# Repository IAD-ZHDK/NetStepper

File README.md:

# Net Stepper

**A networked stepper motor controller.**

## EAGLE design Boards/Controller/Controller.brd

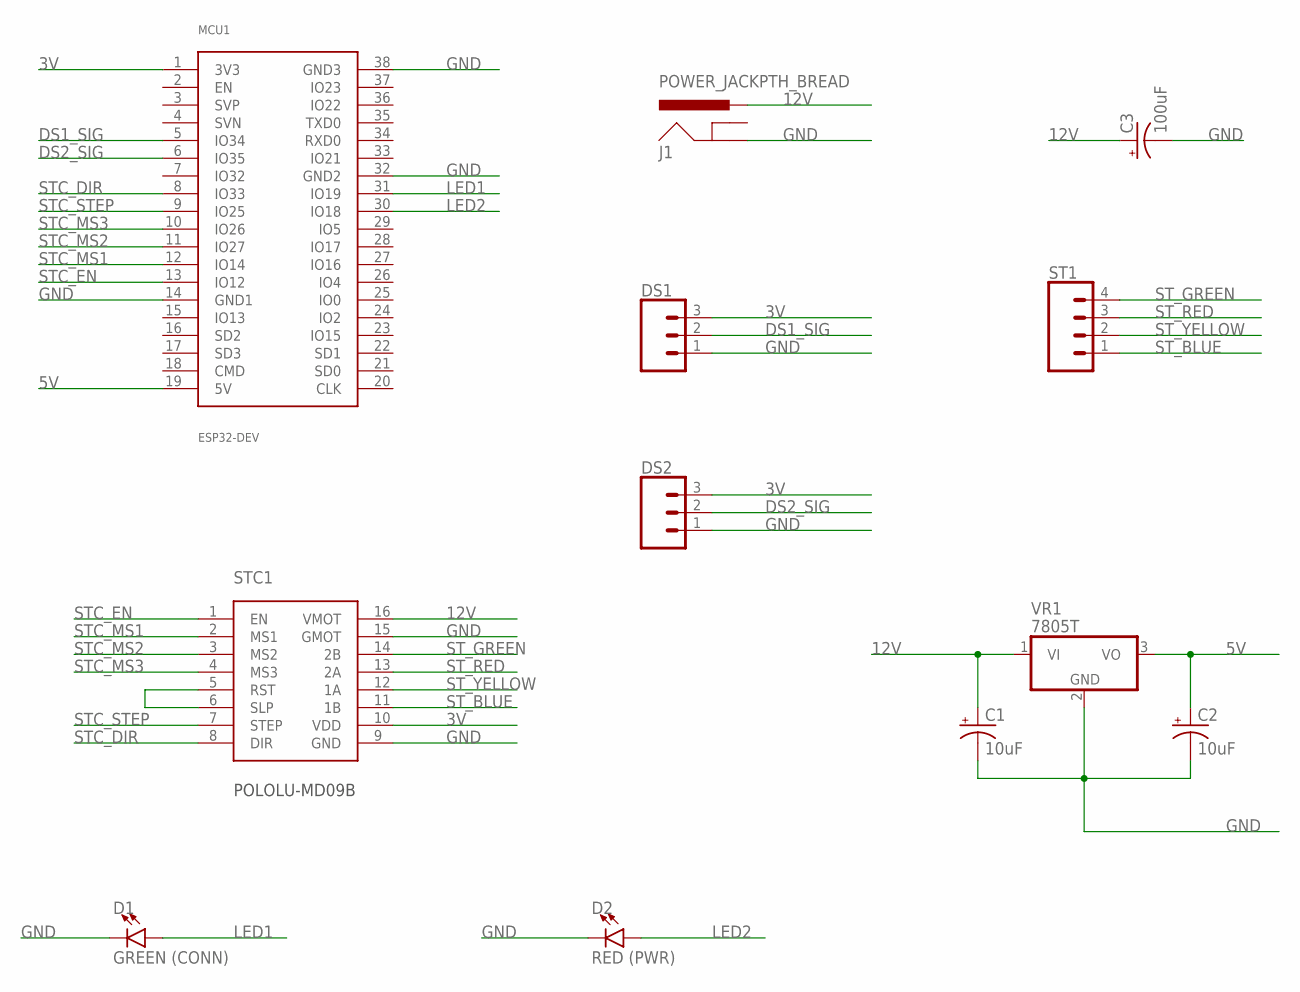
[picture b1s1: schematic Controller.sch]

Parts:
C1, C2: 10uF; E2-5
C3: 100uF; E2-5
D1: GREEN (CONN); LED_5MM
D2: RED (PWR); LED_5MM
DS1, DS2: CONN_03LONGPADS; 1X03_LONGPADS
J1: POWER_JACKPTH_BREAD; POWER_JACK_PTH_BREAD
MCU1: ESP32-DEV
ST1: CONN_04LONGPADS; 1X04_LONGPADS
STC1: POLOLU-MD09B
VR1: 7805T; TO220H

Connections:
3V: DS1.3, DS2.3, MCU1.1 (3V3), STC1.10 (VDD)
5V: C2.+, MCU1.19 (5V), VR1.3 (VO)
12V: C1.+, C3.+, J1.PWR, STC1.16 (VMOT), VR1.1 (VI)
DS1_SIG: DS1.2, MCU1.5 (IO34)
DS2_SIG: DS2.2, MCU1.6 (IO35)
GND: C1.-, C2.-, C3.-, D1.K (C), D2.K (C), DS1.1, DS2.1, J1.GND, MCU1.14 (GND1), MCU1.32 (GND2), MCU1.38 (GND3), STC1.9 (GND), STC1.15 (GMOT), VR1.2 (GND)
LED1: D1.A, MCU1.31 (IO19)
LED2: D2.A, MCU1.30 (IO18)
unnamed: STC1.5 (RST), STC1.6 (SLP)
STC_DIR: MCU1.8 (IO33), STC1.8 (DIR)
STC_EN: MCU1.13 (IO12), STC1.1 (EN)
STC_MS1: MCU1.12 (IO14), STC1.2 (MS1)
STC_MS2: MCU1.11 (IO27), STC1.3 (MS2)
STC_MS3: MCU1.10 (IO26), STC1.4 (MS3)
STC_STEP: MCU1.9 (IO25), STC1.7 (STEP)
ST_BLUE: ST1.1, STC1.11 (1B)
ST_GREEN: ST1.4, STC1.14 (2B)
ST_RED: ST1.3, STC1.13 (2A)
ST_YELLOW: ST1.2, STC1.12 (1A)

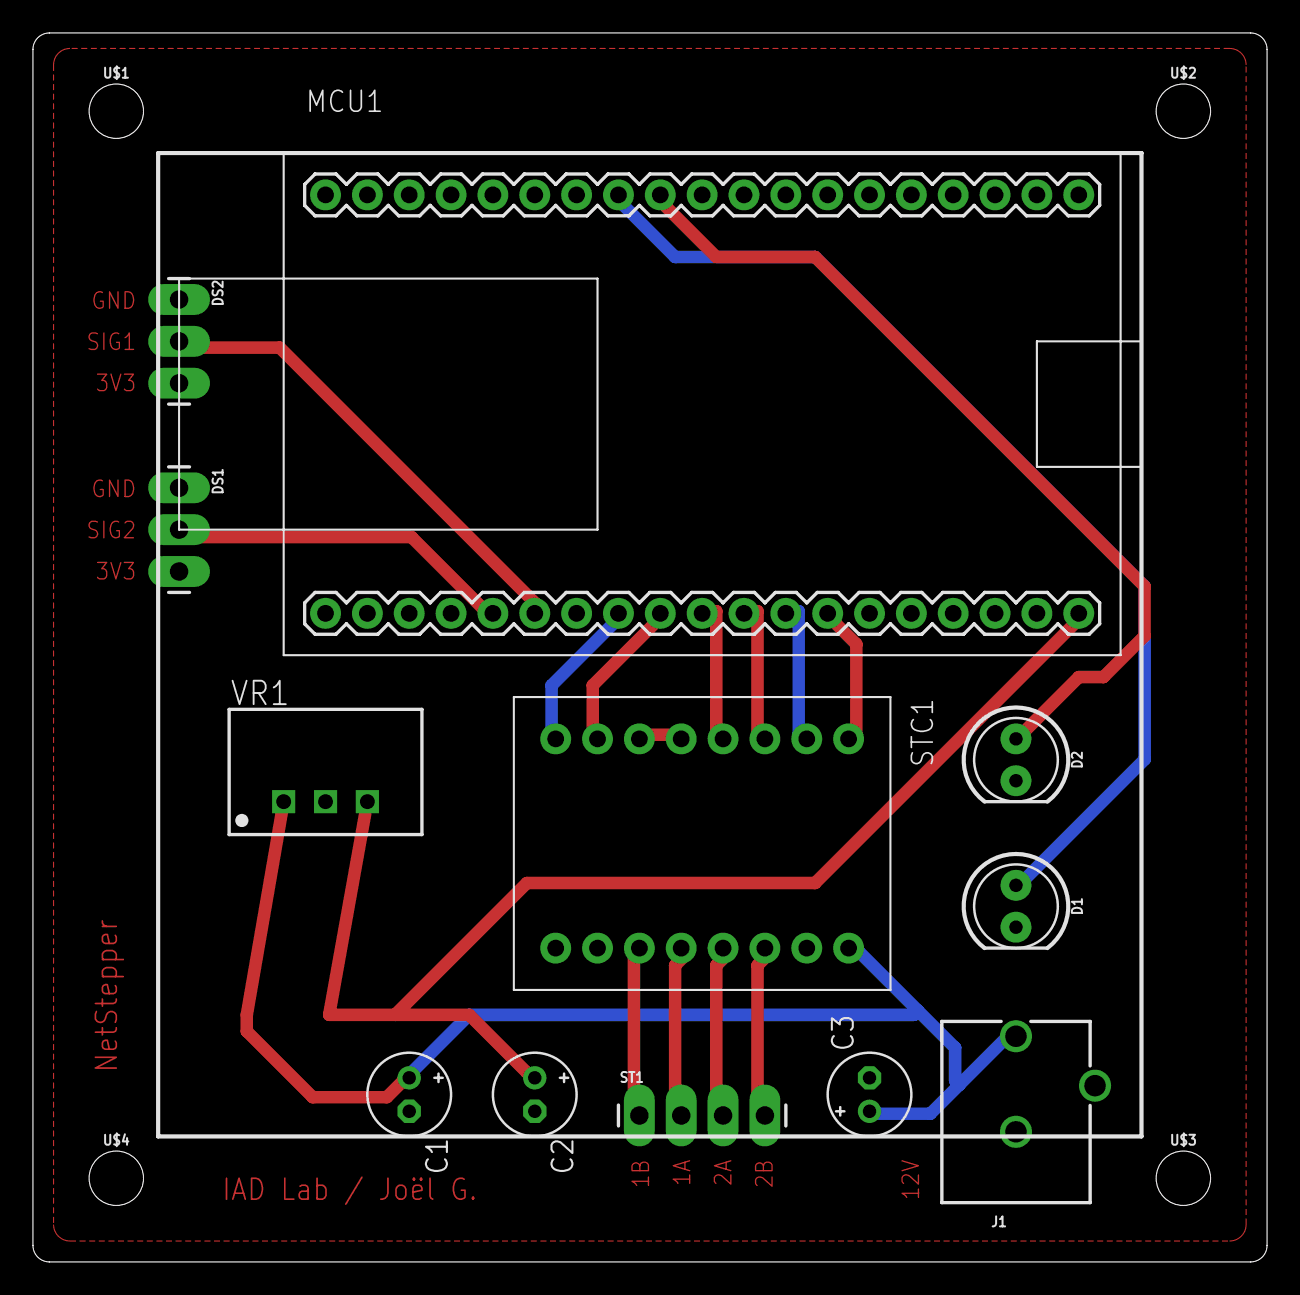
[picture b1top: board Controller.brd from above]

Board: 2 copper layers, 74.9 x 74.6 mm, 16 parts (0 on the bottom side), 19 nets.

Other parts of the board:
U$1, U$2, U$3, U$4: STAND-OFF

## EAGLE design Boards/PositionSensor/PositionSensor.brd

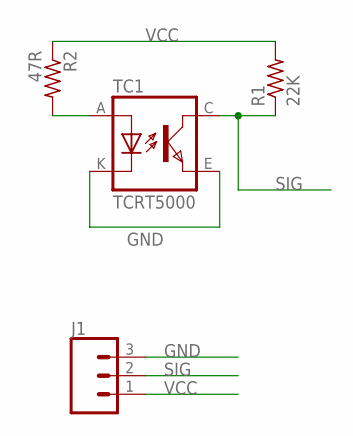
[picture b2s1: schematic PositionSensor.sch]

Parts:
J1: CONN_03LONGPADS; 1X03_LONGPADS
R1: 22K; 0204/7
R2: 47R; 0204/7
TC1: TCRT5000

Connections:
GND: J1.3, TC1.E (EMITTER), TC1.K (CATHODE)
unnamed: R2.2, TC1.A (ANODE)
SIG: J1.2, R1.1, TC1.C (COLLECTOR)
VCC: J1.1, R1.2, R2.1

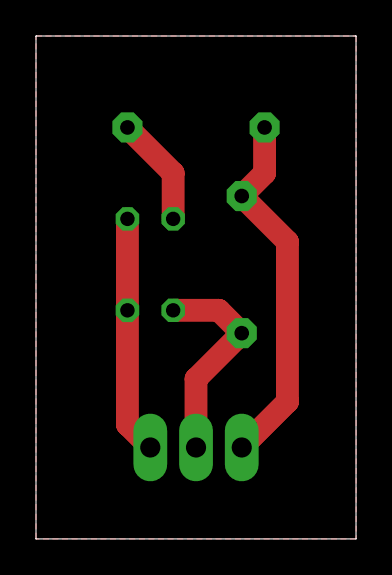
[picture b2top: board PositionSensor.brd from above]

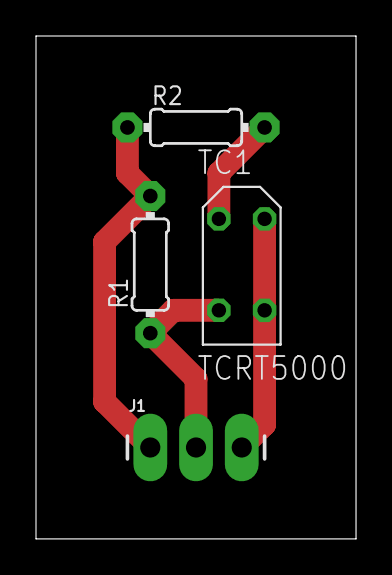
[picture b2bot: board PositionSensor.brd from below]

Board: 2 copper layers, 17.8 x 27.9 mm, 4 parts (4 on the bottom side), 4 nets.

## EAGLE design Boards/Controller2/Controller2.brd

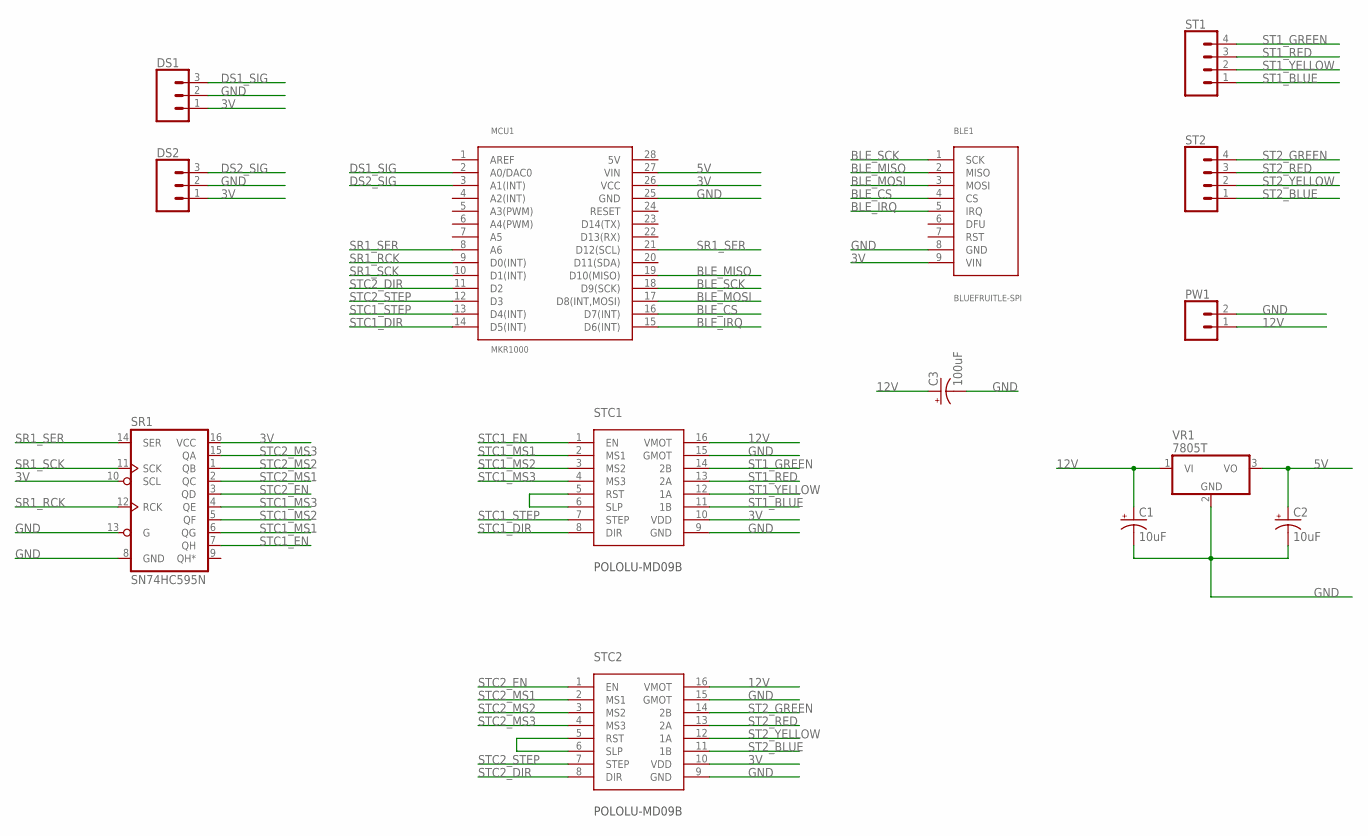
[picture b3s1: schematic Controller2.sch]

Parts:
BLE1: BLUEFRUITLE-SPI; BLUEFRUITLE-SPI-SOCKET
C1, C2: 10uF; E2-5
C3: 100uF; E2-5
DS1, DS2: CONN_03LONGPADS; 1X03_LONGPADS
MCU1: MKR1000; MKR1000-SOCKET
PW1: CONN_025MM; SCREWTERMINAL-5MM-2
SR1: SN74HC595N; DIP16
ST1, ST2: CONN_04LONGPADS; 1X04_LONGPADS
STC1, STC2: POLOLU-MD09B
VR1: 7805T; TO220H

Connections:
3V: BLE1.9 (VIN), DS1.1, DS2.1, MCU1.26 (VCC), SR1.10 (SCL), SR1.16 (VCC), STC1.10 (VDD), STC2.10 (VDD)
5V: C2.+, MCU1.27 (VIN), VR1.3 (VO)
12V: C1.+, C3.+, PW1.1, STC1.16 (VMOT), STC2.16 (VMOT), VR1.1 (VI)
BLE_CS: BLE1.4 (CS), MCU1.16 (D7(INT))
BLE_IRQ: BLE1.5 (IRQ), MCU1.15 (D6(INT))
BLE_MISO: BLE1.2 (MISO), MCU1.19 (D10(MISO))
BLE_MOSI: BLE1.3 (MOSI), MCU1.17 (D8(INT,MOSI))
BLE_SCK: BLE1.1 (SCK), MCU1.18 (D9(SCK))
DS1_SIG: DS1.3, MCU1.2 (A0/DAC0)
DS2_SIG: DS2.3, MCU1.3 (A1(INT))
GND: BLE1.8 (GND), C1.-, C2.-, C3.-, DS1.2, DS2.2, MCU1.25 (GND), PW1.2, SR1.8 (GND), SR1.13 (G), STC1.9 (GND), STC1.15 (GMOT), STC2.9 (GND), STC2.15 (GMOT), VR1.2 (GND)
unnamed: STC1.5 (RST), STC1.6 (SLP)
unnamed: STC2.5 (RST), STC2.6 (SLP)
SR1_RCK: MCU1.9 (D0(INT)), SR1.12 (RCK)
SR1_SCK: MCU1.10 (D1(INT)), SR1.11 (SCK)
SR1_SER: MCU1.8 (A6), MCU1.21 (D12(SCL)), SR1.14 (SER)
ST1_BLUE: ST1.1, STC1.11 (1B)
ST1_GREEN: ST1.4, STC1.14 (2B)
ST1_RED: ST1.3, STC1.13 (2A)
ST1_YELLOW: ST1.2, STC1.12 (1A)
ST2_BLUE: ST2.1, STC2.11 (1B)
ST2_GREEN: ST2.4, STC2.14 (2B)
ST2_RED: ST2.3, STC2.13 (2A)
ST2_YELLOW: ST2.2, STC2.12 (1A)
STC1_DIR: MCU1.14 (D5(INT)), STC1.8 (DIR)
STC1_EN: SR1.7 (QH), STC1.1 (EN)
STC1_MS1: SR1.6 (QG), STC1.2 (MS1)
STC1_MS2: SR1.5 (QF), STC1.3 (MS2)
STC1_MS3: SR1.4 (QE), STC1.4 (MS3)
STC1_STEP: MCU1.13 (D4(INT)), STC1.7 (STEP)
STC2_DIR: MCU1.11 (D2), STC2.8 (DIR)
STC2_EN: SR1.3 (QD), STC2.1 (EN)
STC2_MS1: SR1.2 (QC), STC2.2 (MS1)
STC2_MS2: SR1.1 (QB), STC2.3 (MS2)
STC2_MS3: SR1.15 (QA), STC2.4 (MS3)
STC2_STEP: MCU1.12 (D3), STC2.7 (STEP)

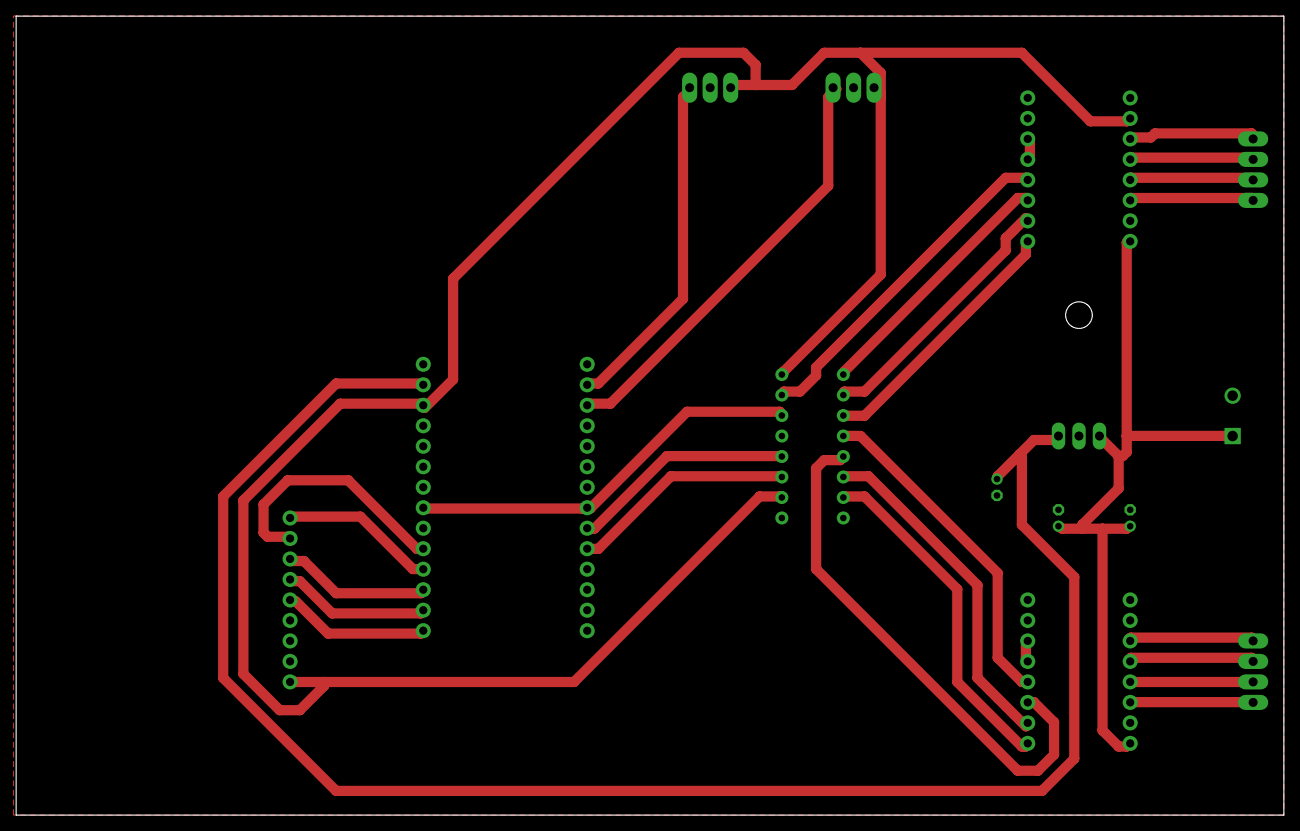
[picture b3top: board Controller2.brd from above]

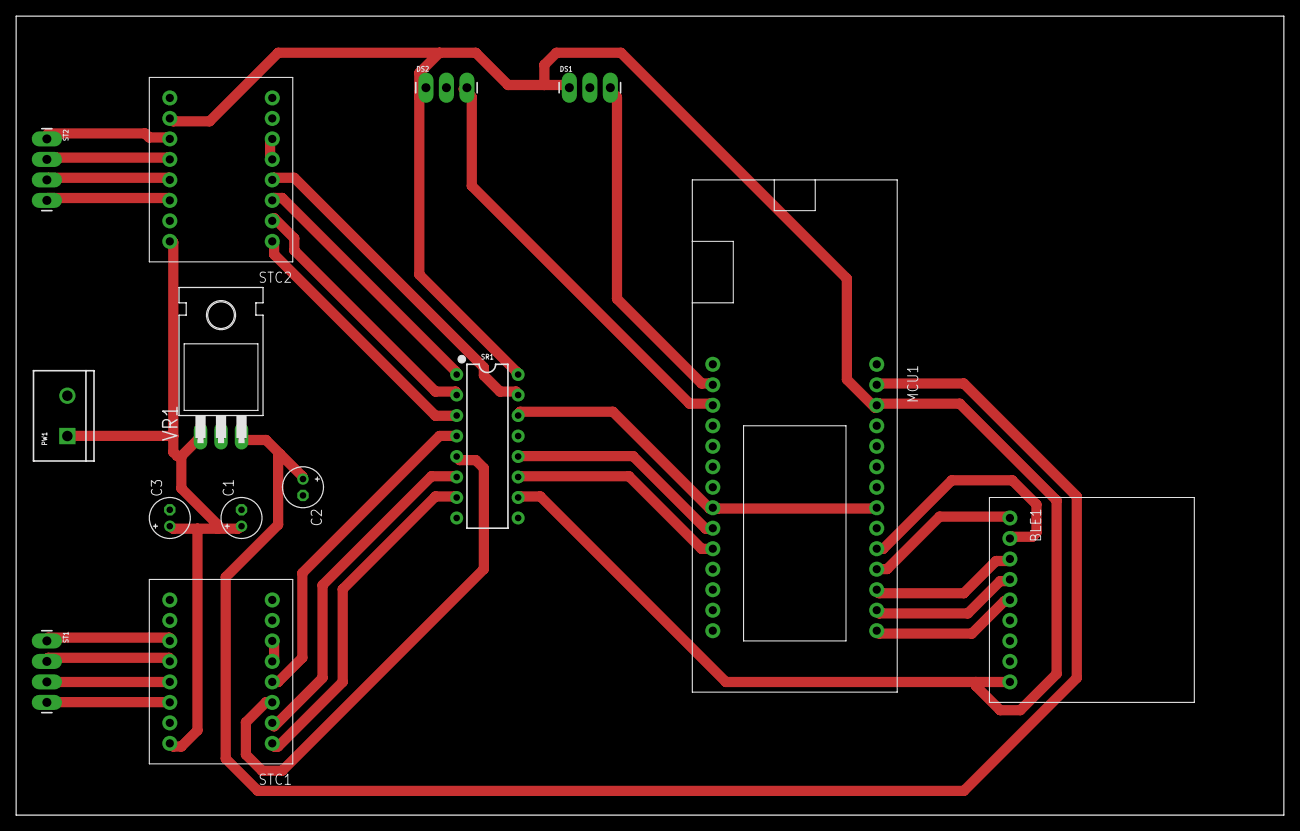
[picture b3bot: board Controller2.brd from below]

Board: 2 copper layers, 157.1 x 99.0 mm, 14 parts (14 on the bottom side), 36 nets.

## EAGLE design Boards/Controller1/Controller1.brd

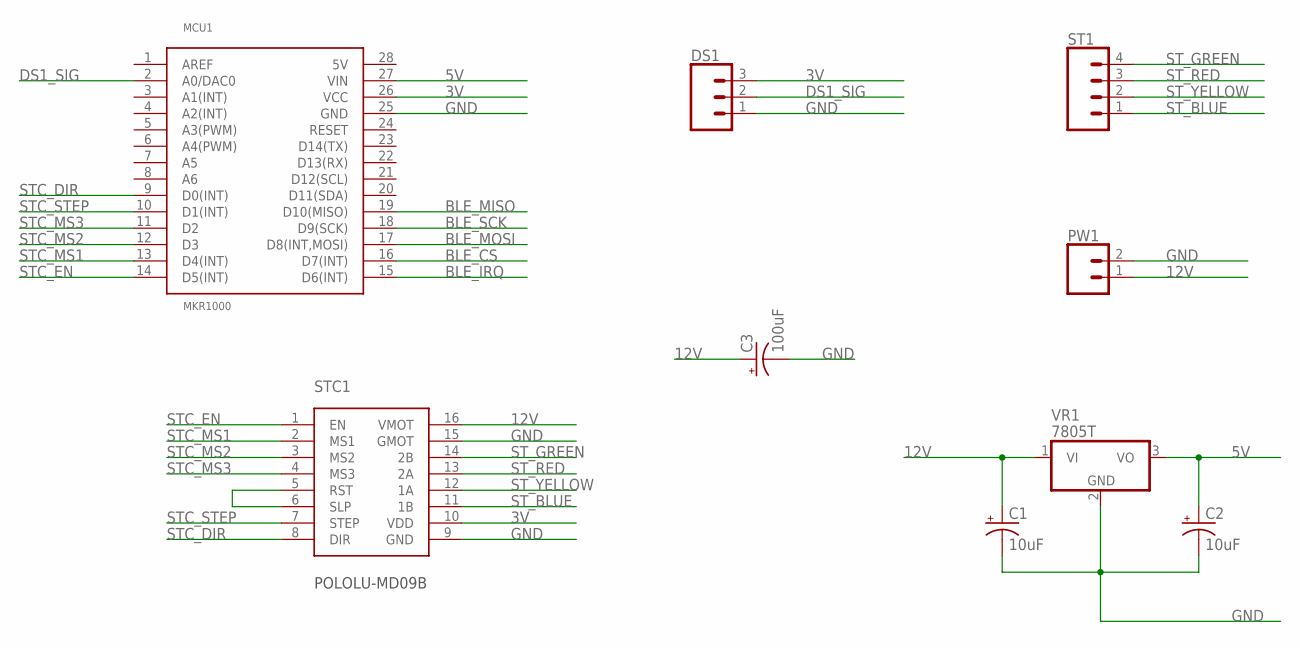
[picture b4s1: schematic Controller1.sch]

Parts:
C1, C2: 10uF; E2-5
C3: 100uF; E2-5
DS1: CONN_03LONGPADS; 1X03_LONGPADS
MCU1: MKR1000; MKR1000-SOCKET
PW1: CONN_025MM; SCREWTERMINAL-5MM-2
ST1: CONN_04LONGPADS; 1X04_LONGPADS
STC1: POLOLU-MD09B
VR1: 7805T; TO220H

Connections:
3V: DS1.3, MCU1.26 (VCC), STC1.10 (VDD)
5V: C2.+, MCU1.27 (VIN), VR1.3 (VO)
12V: C1.+, C3.+, PW1.1, STC1.16 (VMOT), VR1.1 (VI)
BLE_CS: MCU1.16 (D7(INT))
BLE_IRQ: MCU1.15 (D6(INT))
BLE_MISO: MCU1.19 (D10(MISO))
BLE_MOSI: MCU1.17 (D8(INT,MOSI))
BLE_SCK: MCU1.18 (D9(SCK))
DS1_SIG: DS1.2, MCU1.2 (A0/DAC0)
GND: C1.-, C2.-, C3.-, DS1.1, MCU1.25 (GND), PW1.2, STC1.9 (GND), STC1.15 (GMOT), VR1.2 (GND)
unnamed: STC1.5 (RST), STC1.6 (SLP)
STC_DIR: MCU1.9 (D0(INT)), STC1.8 (DIR)
STC_EN: MCU1.14 (D5(INT)), STC1.1 (EN)
STC_MS1: MCU1.13 (D4(INT)), STC1.2 (MS1)
STC_MS2: MCU1.12 (D3), STC1.3 (MS2)
STC_MS3: MCU1.11 (D2), STC1.4 (MS3)
STC_STEP: MCU1.10 (D1(INT)), STC1.7 (STEP)
ST_BLUE: ST1.1, STC1.11 (1B)
ST_GREEN: ST1.4, STC1.14 (2B)
ST_RED: ST1.3, STC1.13 (2A)
ST_YELLOW: ST1.2, STC1.12 (1A)

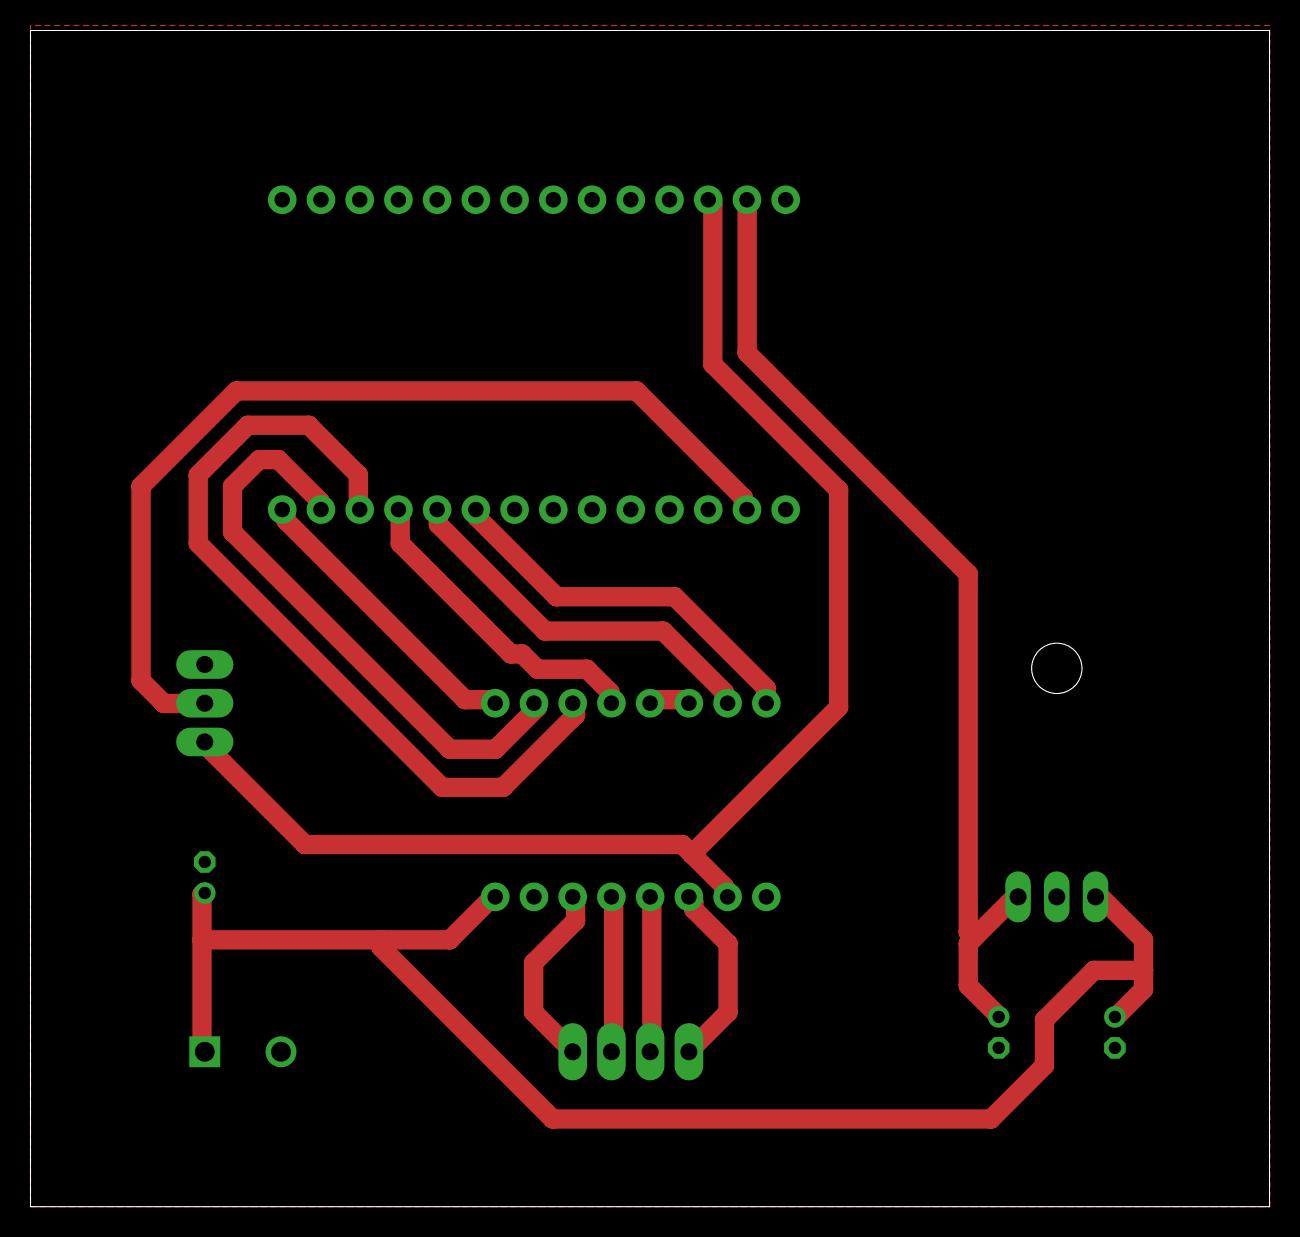
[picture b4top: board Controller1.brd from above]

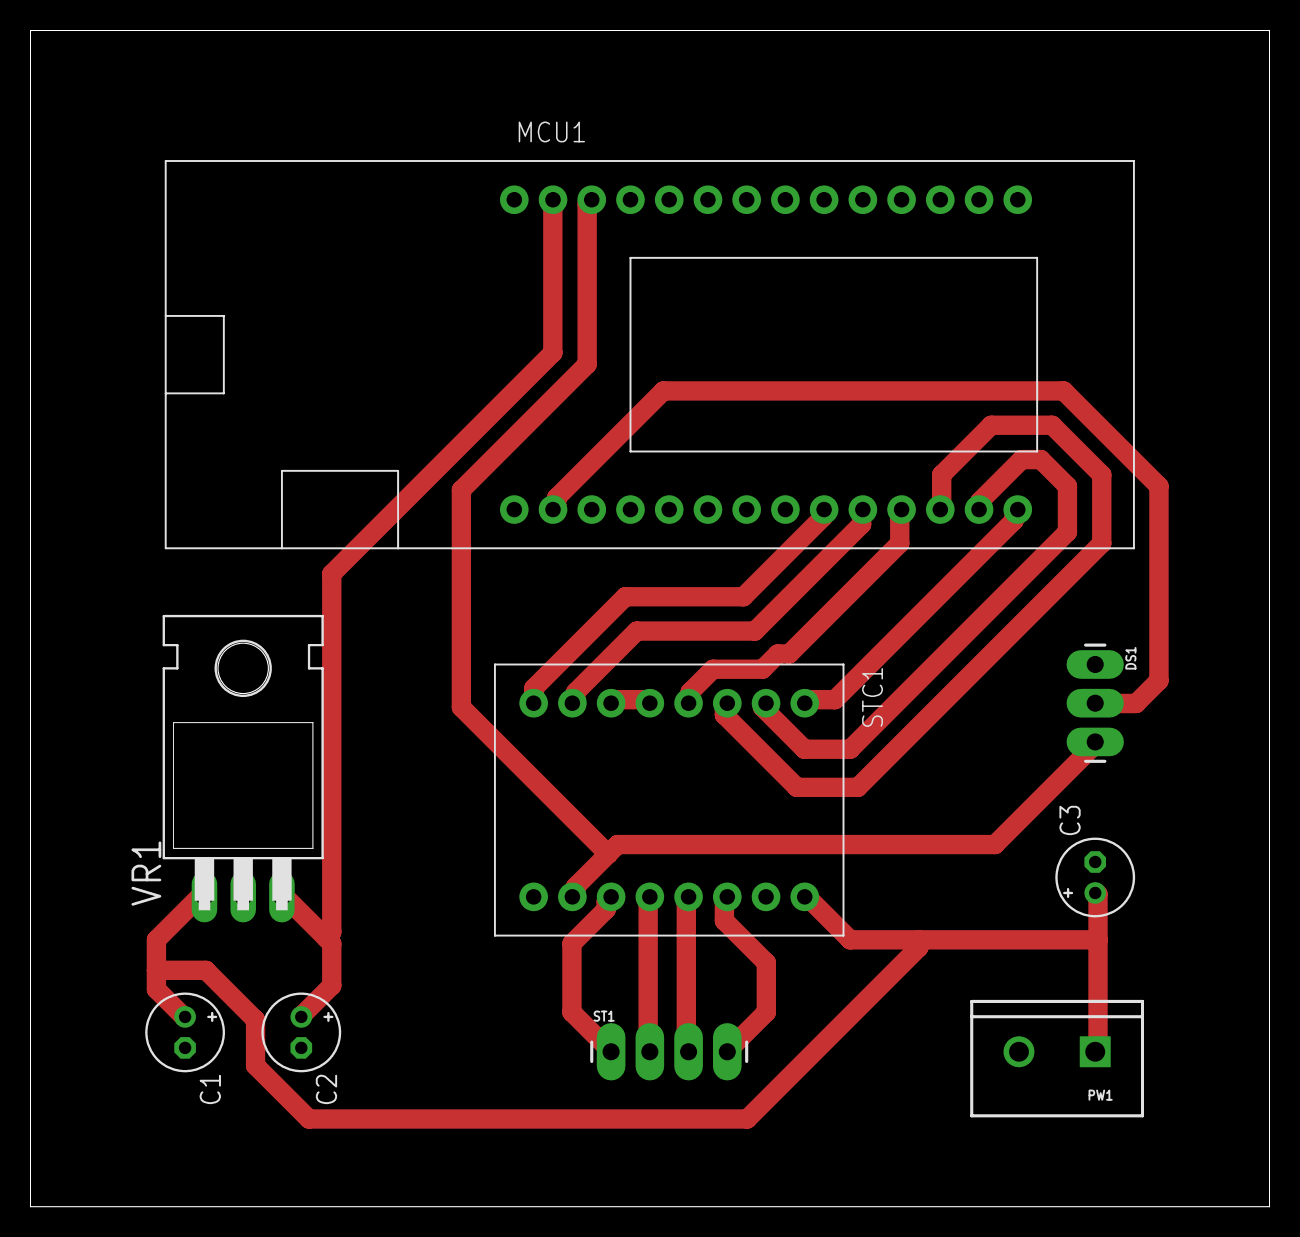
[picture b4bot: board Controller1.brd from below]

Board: 2 copper layers, 81.3 x 77.1 mm, 9 parts (9 on the bottom side), 16 nets.

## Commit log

2017-02-15 added boards
2017-02-15 added latest code
2017-02-15 removed obsolete signals
2017-02-16 refactored code
2017-02-16 fixed typo
2017-02-16 format
2017-02-16 added notes
2017-02-16 simplified
2017-02-16 emit sensor reading
2017-02-16 cleaned up and added some docs
2017-02-16 added drive mode
2017-02-16 support for single step mode
2017-02-16 added working absolute positioning
2017-02-16 use cw and ccw to make direction clear
2017-02-16 renamed enable to power
2017-02-16 removed single stepping
2017-02-16 fix names
2017-02-16 removed direct mode control
2017-02-16 refactored
2017-02-16 added writeStep method
2017-02-16 fix last stuff
2017-02-20 decrease messages sent out
2017-02-22 do nothing if state is unset
2017-02-24 updated gcode
2017-02-24 updated position sensor
2017-02-24 cleaned up some stuff
2017-03-02 finished esp32 based board
2017-03-02 finish esp32 based controller
2017-03-13 finished esp32 board based board
2017-03-13 finished for mass production
2017-03-13 finished controller for mass production
2017-03-14 added dynamic topics
2017-03-14 swapped
2017-03-14 use compiler based string concatenation
2017-03-16 changed labels
2017-03-16 use stepping voltage regulator instead of a linear
2017-03-26 removed outdated code
2017-03-26 moved files
2017-06-30 added net stepper firmware source code
2017-06-30 simplified cmake setup
2017-06-30 update cmake file
2017-07-01 reflect changes to cli
2017-07-03 added missing firmware version
2017-07-03 fix default frequency
2017-07-13 allow frequency between 100 and 10000
2018-01-25 added missing keys
2018-01-25 updated code
2018-01-25 fixed parameter
2018-01-25 added and used art32 library

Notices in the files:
parts and their libraries:
SparkFun-Connectors: Licensing: Creative Commons ShareAlike 4.0 International - https://creativecommons.org/licenses/by-sa/4.0
